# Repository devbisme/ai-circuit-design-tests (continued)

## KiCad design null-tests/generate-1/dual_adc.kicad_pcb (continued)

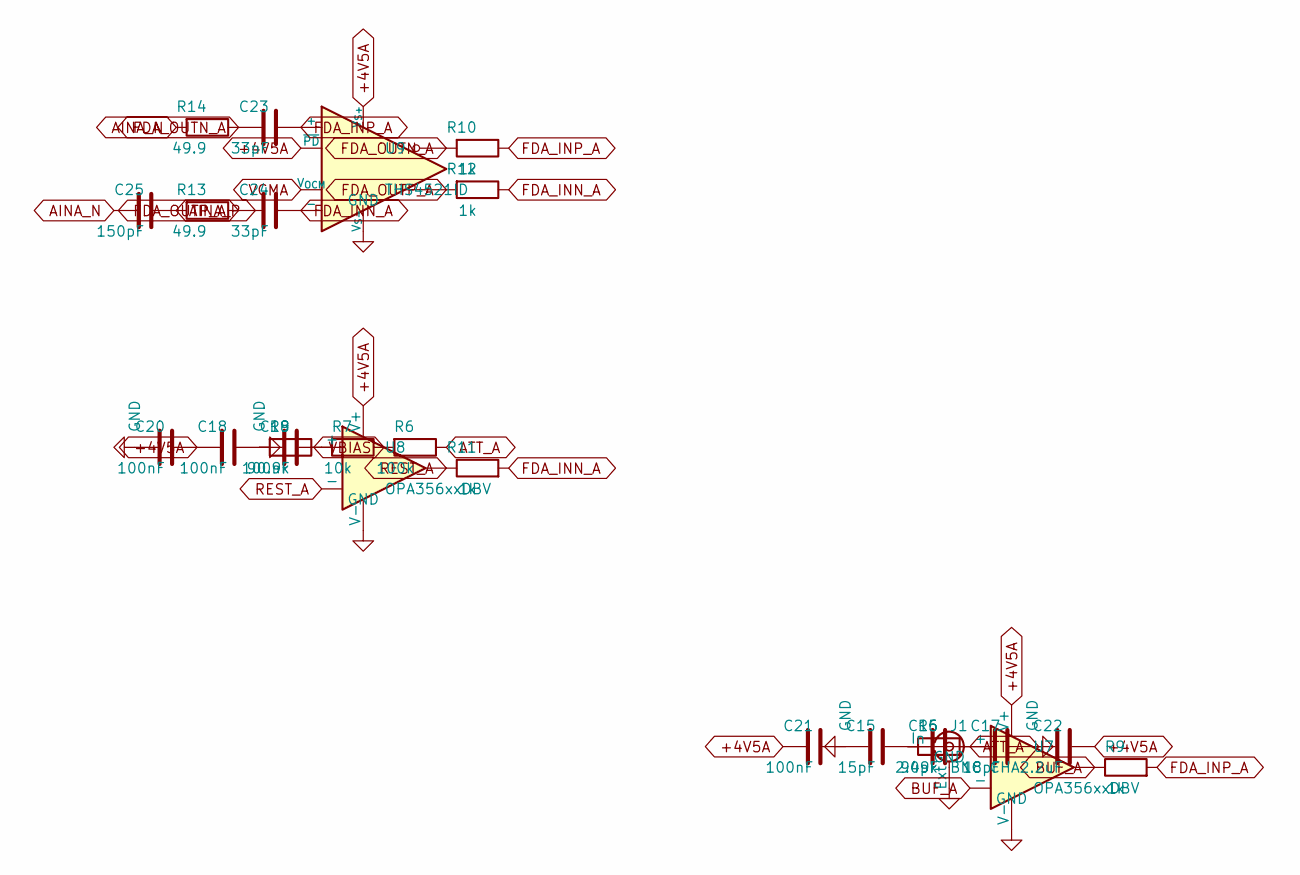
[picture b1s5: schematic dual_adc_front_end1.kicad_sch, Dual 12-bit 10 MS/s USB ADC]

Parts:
C15: 15pF; C_0805_2012Metric
C16: 2.4pF; C_0805_2012Metric
C17: 18pF; C_0603_1608Metric
C18, C20, C21: 100nF; C_0402_1005Metric
C19: 100nF; C_0603_1608Metric
C22: 2.2uF; C_0603_1608Metric
C23, C24: 33pF; C_0603_1608Metric
C25: 150pF; C_0603_1608Metric
J1: BNC CHA; BNC_Amphenol_B6252HB-NPP3G-50_Horizontal
R5: 909k; R_1206_3216Metric
R6: 100k; R_0603_1608Metric
R7: 10k; R_0603_1608Metric
R8: 90.9k; R_0603_1608Metric
R9, R10, R11, R12: 1k; R_0603_1608Metric
R13, R14: 49.9; R_0603_1608Metric
U7, U8: OPA356xxDBV; SOT-23-5
U9: THS4521ID; SOIC-8_3.9x4.9mm_P1.27mm

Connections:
+4V5A: C18.1, C20.1, C21.1, C22.1, U7.5 (V+), U8.5 (V+), U9.3 (V_{S+}), U9.7 (~PD); also elsewhere on the board
AINA_N: C25.2, R14.2; also elsewhere on the board
AINA_P: C25.1, R13.2; also elsewhere on the board
ATT_A: C16.2, C17.1, R5.2, R6.1, U7.3 (+); also elsewhere on the board
BUF_A: R9.1, U7.1, U7.4 (-)
FDA_INN_A: C24.1, R11.2, R12.1, U9.1 (-)
FDA_INP_A: C23.1, R9.2, R10.1, U9.8 (+)
FDA_OUTN_A: C23.2, R10.2, R14.1, U9.5
FDA_OUTP_A: C24.2, R12.2, R13.1, U9.4
GND: C15.2, C17.2, C18.2, C19.2, C20.2, C21.2, C22.2, J1.2 (Ext), R8.2, U7.2 (V-), U8.2 (V-), U9.6 (V_{S-}); also elsewhere on the board
unnamed: C15.1, C16.1, J1.1 (In), R5.1
unnamed: C19.1, R7.2, R8.1, U8.3 (+)
REST_A: R11.1, U8.1, U8.4 (-)
VBIAS: R6.2, R7.1; also elsewhere on the board
VCMA: U9.2 (V_{OCM}); also elsewhere on the board

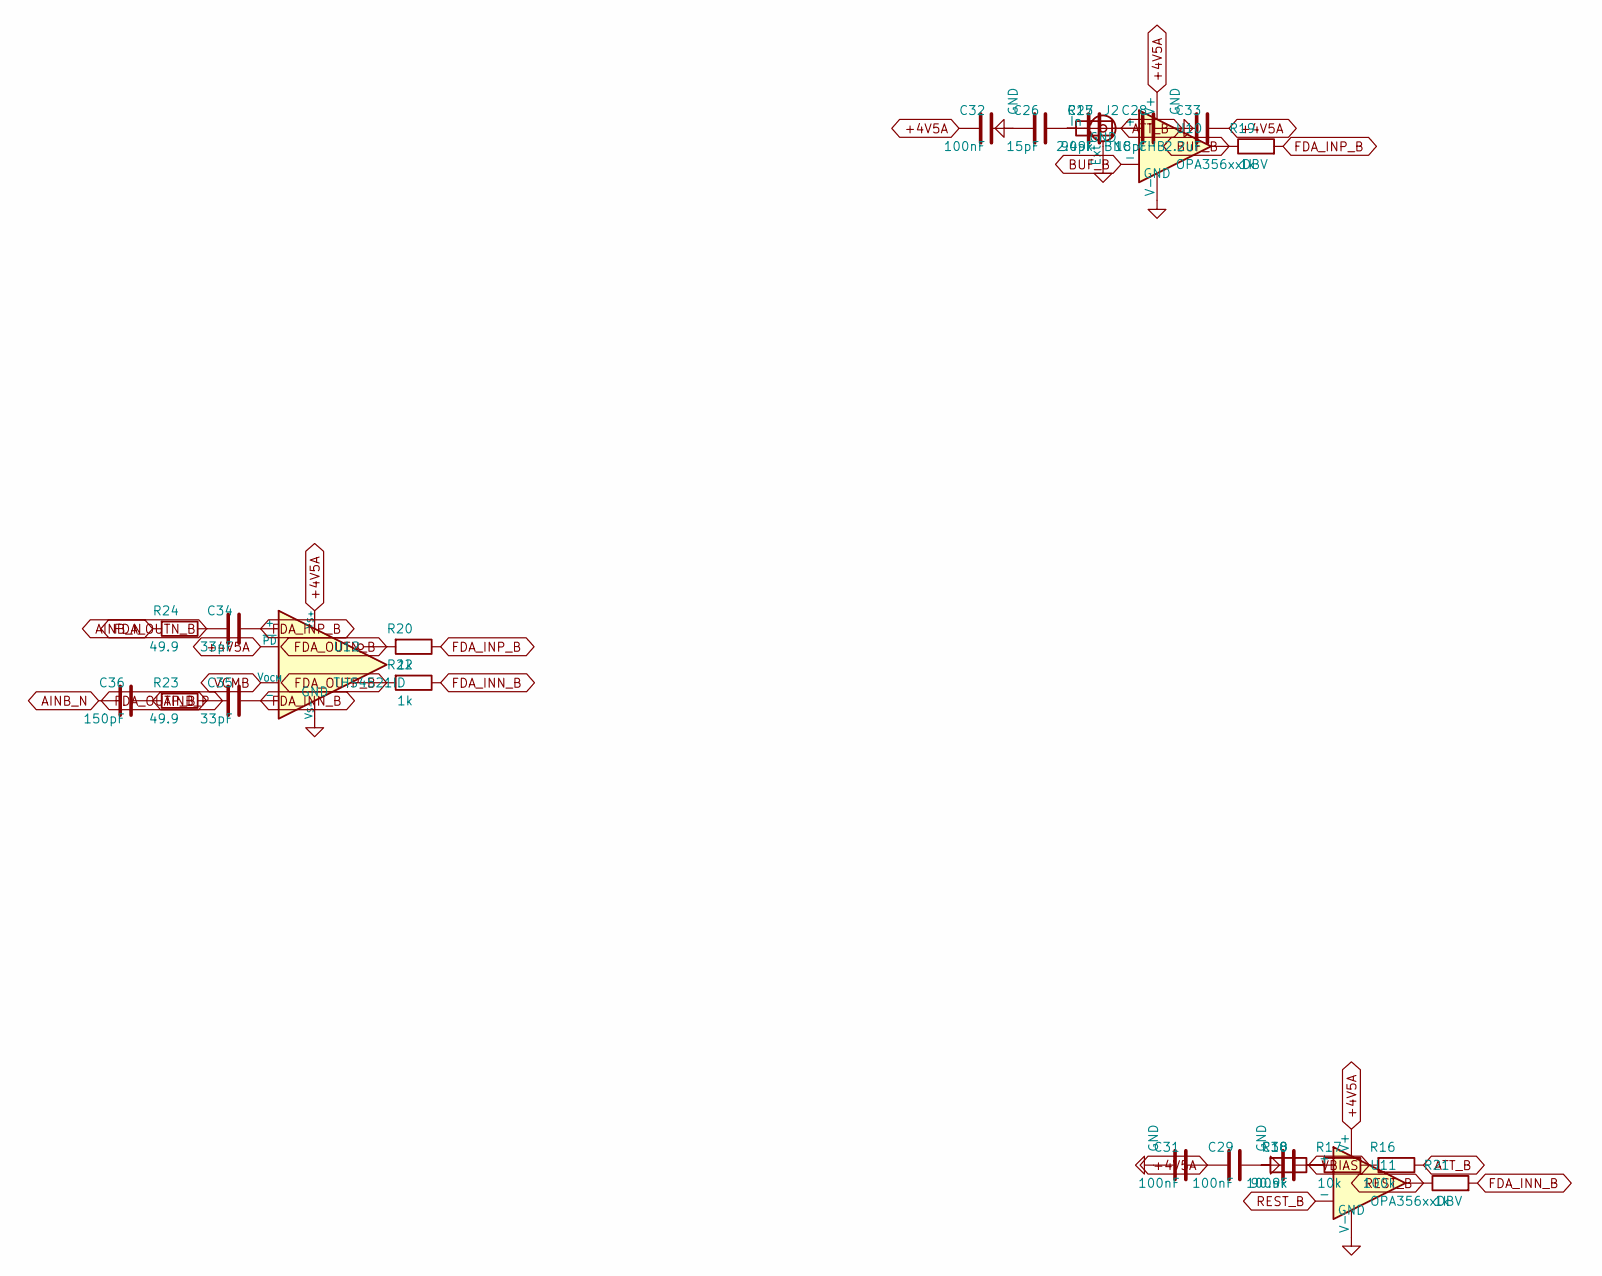
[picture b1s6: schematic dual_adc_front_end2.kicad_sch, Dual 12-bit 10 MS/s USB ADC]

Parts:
C26: 15pF; C_0805_2012Metric
C27: 2.4pF; C_0805_2012Metric
C28: 18pF; C_0603_1608Metric
C29, C31, C32: 100nF; C_0402_1005Metric
C30: 100nF; C_0603_1608Metric
C33: 2.2uF; C_0603_1608Metric
C34, C35: 33pF; C_0603_1608Metric
C36: 150pF; C_0603_1608Metric
J2: BNC CHB; BNC_Amphenol_B6252HB-NPP3G-50_Horizontal
R15: 909k; R_1206_3216Metric
R16: 100k; R_0603_1608Metric
R17: 10k; R_0603_1608Metric
R18: 90.9k; R_0603_1608Metric
R19, R20, R21, R22: 1k; R_0603_1608Metric
R23, R24: 49.9; R_0603_1608Metric
U10, U11: OPA356xxDBV; SOT-23-5
U12: THS4521ID; SOIC-8_3.9x4.9mm_P1.27mm

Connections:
+4V5A: C29.1, C31.1, C32.1, C33.1, U10.5 (V+), U11.5 (V+), U12.3 (V_{S+}), U12.7 (~PD); also elsewhere on the board
AINB_N: C36.2, R24.2; also elsewhere on the board
AINB_P: C36.1, R23.2; also elsewhere on the board
ATT_B: C27.2, C28.1, R15.2, R16.1, U10.3 (+); also elsewhere on the board
BUF_B: R19.1, U10.1, U10.4 (-)
FDA_INN_B: C35.1, R21.2, R22.1, U12.1 (-)
FDA_INP_B: C34.1, R19.2, R20.1, U12.8 (+)
FDA_OUTN_B: C34.2, R20.2, R24.1, U12.5
FDA_OUTP_B: C35.2, R22.2, R23.1, U12.4
GND: C26.2, C28.2, C29.2, C30.2, C31.2, C32.2, C33.2, J2.2 (Ext), R18.2, U10.2 (V-), U11.2 (V-), U12.6 (V_{S-}); also elsewhere on the board
unnamed: C26.1, C27.1, J2.1 (In), R15.1
unnamed: C30.1, R17.2, R18.1, U11.3 (+)
REST_B: R21.1, U11.1, U11.4 (-)
VBIAS: R16.2, R17.1; also elsewhere on the board
VCMB: U12.2 (V_{OCM}); also elsewhere on the board

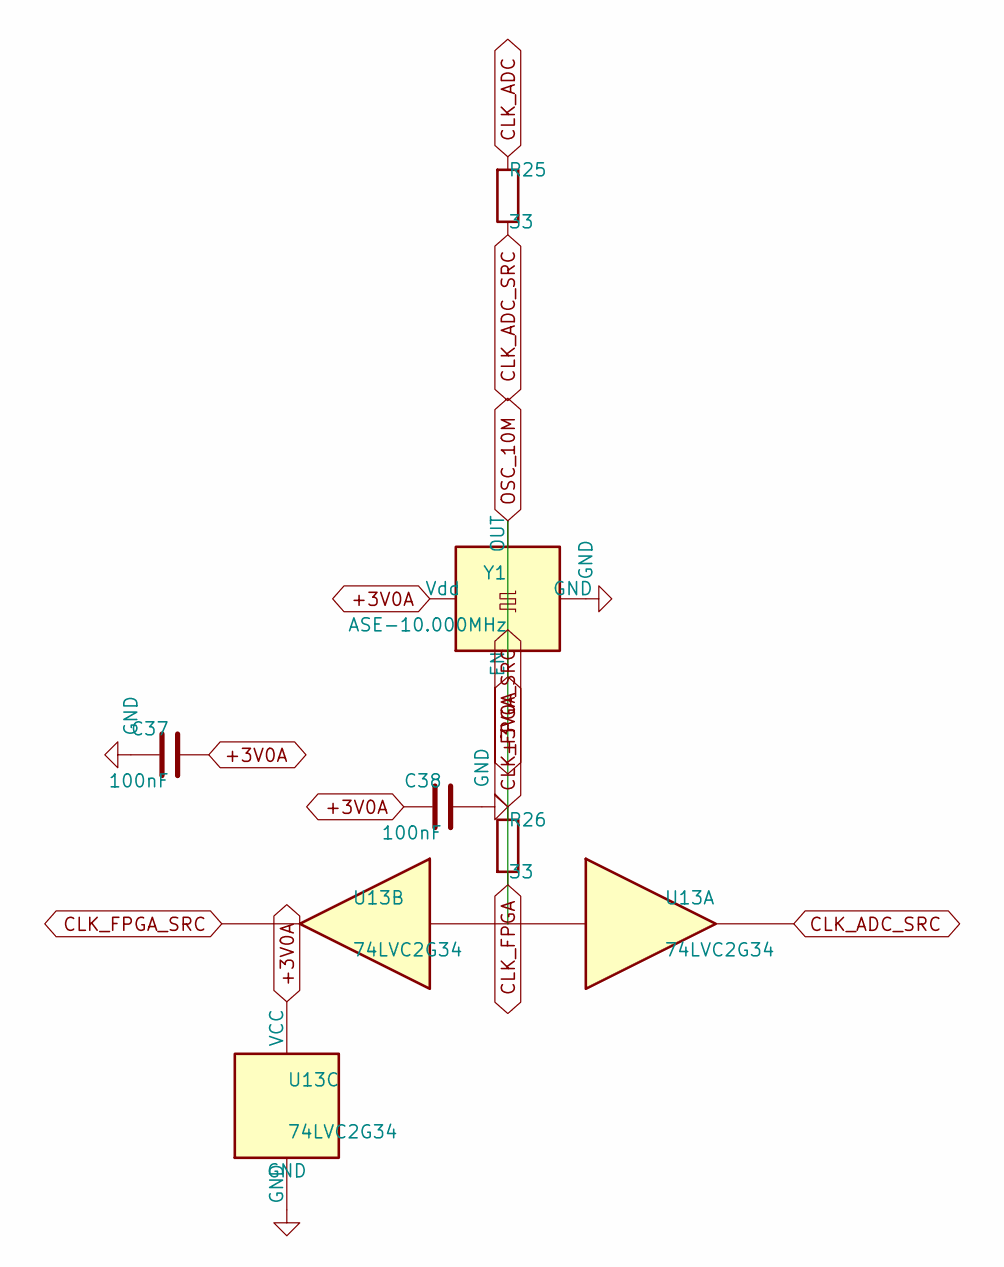
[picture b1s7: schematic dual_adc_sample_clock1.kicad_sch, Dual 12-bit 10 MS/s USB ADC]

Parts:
C37, C38: 100nF; C_0402_1005Metric
R25, R26: 33; R_0603_1608Metric
U13: 74LVC2G34; SOT-363_SC-70-6
Y1: ASE-10.000MHz; Oscillator_SMD_Abracon_ASE-4Pin_3.2x2.5mm

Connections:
CLK_ADC: R25.2; also elsewhere on the board
CLK_ADC_SRC: R25.1, U13.6
GND: C37.2, C38.2, U13.2 (GND), Y1.2 (GND); also elsewhere on the board

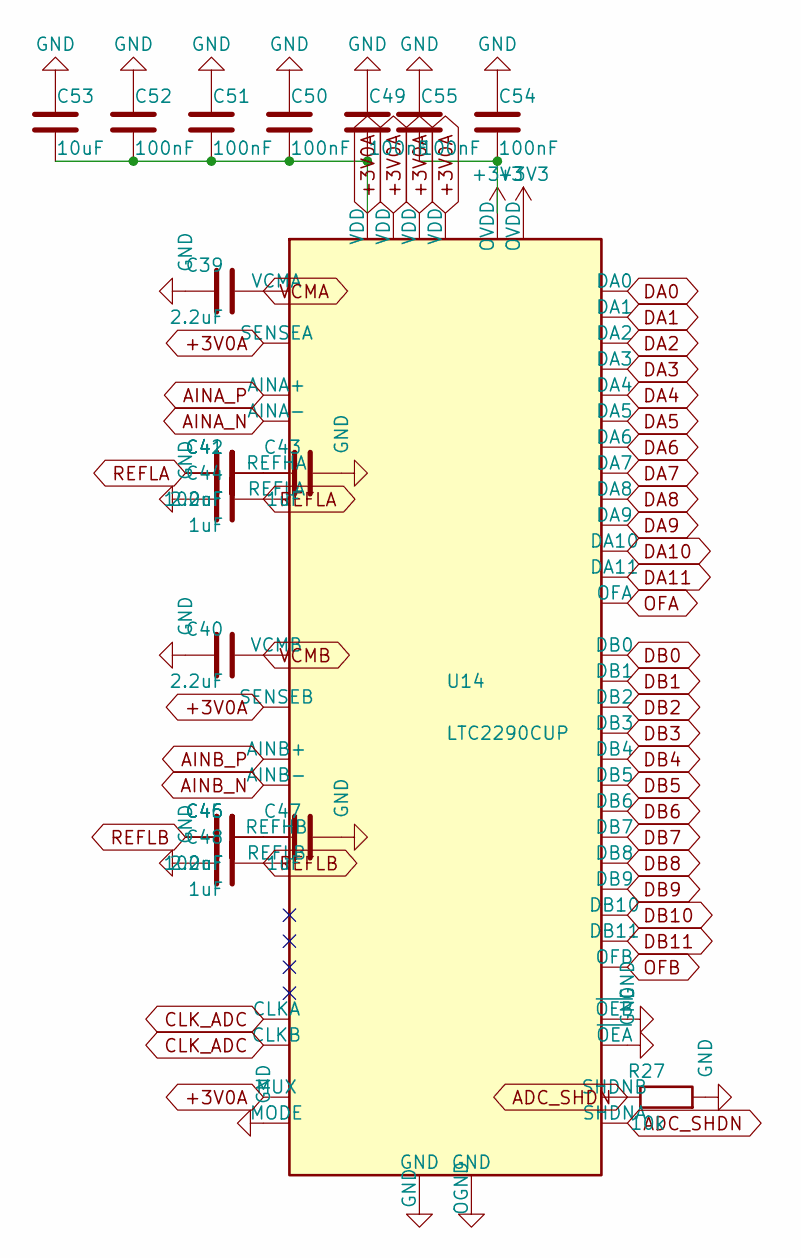
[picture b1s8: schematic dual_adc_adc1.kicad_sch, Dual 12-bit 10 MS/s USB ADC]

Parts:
C39, C40, C42, C46: 2.2uF; C_0603_1608Metric
C41, C45, C49, C50, C51, C52, C54, C55: 100nF; C_0402_1005Metric
C43, C44, C47, C48: 1uF; C_0603_1608Metric
C53: 10uF; C_0805_2012Metric
R27: 10k; R_0603_1608Metric
U14: LTC2290CUP; QFN-64-1EP_9x9mm_P0.5mm_EP7.15x7.15mm

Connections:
+3V3: C54.1, C55.1, U14.32 (OVDD), U14.49 (OVDD); also elsewhere on the board
ADC_SHDN: R27.1, U14.22 (SHDNB), U14.59 (SHDNA); also elsewhere on the board
AINA_N: U14.2 (AINA-); also elsewhere on the board
AINA_P: U14.1 (AINA+); also elsewhere on the board
AINB_N: U14.15 (AINB-); also elsewhere on the board
AINB_P: U14.16 (AINB+); also elsewhere on the board
CLK_ADC: U14.8 (CLKA), U14.9 (CLKB); also elsewhere on the board
DA0: U14.43 (DA0); also elsewhere on the board
DA1: U14.44 (DA1); also elsewhere on the board
DA2: U14.45 (DA2); also elsewhere on the board
DA3: U14.46 (DA3); also elsewhere on the board
DA4: U14.47 (DA4); also elsewhere on the board
DA5: U14.48 (DA5); also elsewhere on the board
DA6: U14.51 (DA6); also elsewhere on the board
DA7: U14.52 (DA7); also elsewhere on the board
DA8: U14.53 (DA8); also elsewhere on the board
DA9: U14.54 (DA9); also elsewhere on the board
DA10: U14.55 (DA10); also elsewhere on the board
DA11: U14.56 (DA11); also elsewhere on the board
DB0: U14.26 (DB0); also elsewhere on the board
DB1: U14.27 (DB1); also elsewhere on the board
DB2: U14.28 (DB2); also elsewhere on the board
DB3: U14.29 (DB3); also elsewhere on the board
DB4: U14.30 (DB4); also elsewhere on the board
DB5: U14.33 (DB5); also elsewhere on the board
DB6: U14.34 (DB6); also elsewhere on the board
DB7: U14.35 (DB7); also elsewhere on the board
DB8: U14.36 (DB8); also elsewhere on the board
DB9: U14.37 (DB9); also elsewhere on the board
DB10: U14.38 (DB10); also elsewhere on the board
DB11: U14.39 (DB11); also elsewhere on the board
GND: C39.2, C40.2, C43.2, C44.2, C47.2, C48.2, C49.2, C50.2, C51.2, C52.2, C53.2, C54.2, C55.2, R27.2, U14.17 (GND), U14.23 (~OEB), U14.31 (OGND), U14.50 (OGND), U14.58 (~OEA), U14.60 (MODE), U14.64 (GND), U14.65 (GND); also elsewhere on the board
unnamed: C41.1, C42.1, C43.1, U14.3 (REFHA), U14.4 (REFHA)
unnamed: C45.1, C46.1, C47.1, U14.13 (REFHB), U14.14 (REFHB)
OFA: U14.57 (OFA); also elsewhere on the board
OFB: U14.40 (OFB); also elsewhere on the board
REFLA: C41.2, C42.2, C44.1, U14.5 (REFLA), U14.6 (REFLA)
REFLB: C45.2, C46.2, C48.1, U14.11 (REFLB), U14.12 (REFLB)
VCMA: C39.1, U14.61 (VCMA); also elsewhere on the board
VCMB: C40.1, U14.20 (VCMB); also elsewhere on the board

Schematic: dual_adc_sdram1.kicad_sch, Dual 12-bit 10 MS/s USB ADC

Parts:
C56, C57, C58, C59, C60, C61, C62: 100nF; C_0402_1005Metric
C63: 10uF; C_0805_2012Metric
U15: IS42S16400J-7TL; TSOP-II-54_22.2x10.16mm_P0.8mm

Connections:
+3V3: C56.1, C57.1, C58.1, C59.1, C60.1, C61.1, C62.1, C63.1, U15.1 (VDD), U15.3 (VDDQ), U15.9 (VDDQ), U15.14 (VDD), U15.27 (VDD), U15.43 (VDDQ), U15.49 (VDDQ); also elsewhere on the board
GND: C56.2, C57.2, C58.2, C59.2, C60.2, C61.2, C62.2, C63.2, U15.6 (GNDQ), U15.12 (GNDQ), U15.28 (GND), U15.41 (GND), U15.46 (GNDQ), U15.52 (GNDQ), U15.54 (GND); also elsewhere on the board
SD_A0: U15.23 (A0); also elsewhere on the board
SD_A1: U15.24 (A1); also elsewhere on the board
SD_A2: U15.25 (A2); also elsewhere on the board
SD_A3: U15.26 (A3); also elsewhere on the board
SD_A4: U15.29 (A4); also elsewhere on the board
SD_A5: U15.30 (A5); also elsewhere on the board
SD_A6: U15.31 (A6); also elsewhere on the board
SD_A7: U15.32 (A7); also elsewhere on the board
SD_A8: U15.33 (A8); also elsewhere on the board
SD_A9: U15.34 (A9); also elsewhere on the board
SD_A10: U15.22 (A10); also elsewhere on the board
SD_A11: U15.35 (A11); also elsewhere on the board
SD_BA0: U15.20 (BA0); also elsewhere on the board
SD_BA1: U15.21 (BA1); also elsewhere on the board
SD_CAS_N: U15.17 (~CAS); also elsewhere on the board
SD_CKE: U15.37 (CKE); also elsewhere on the board
SD_CLK: U15.38 (CLK); also elsewhere on the board
SD_CS_N: U15.19 (~CS); also elsewhere on the board
SD_DQ0: U15.2 (DQ0); also elsewhere on the board
SD_DQ1: U15.4 (DQ1); also elsewhere on the board
SD_DQ2: U15.5 (DQ2); also elsewhere on the board
SD_DQ3: U15.7 (DQ3); also elsewhere on the board
SD_DQ4: U15.8 (DQ4); also elsewhere on the board
SD_DQ5: U15.10 (DQ5); also elsewhere on the board
SD_DQ6: U15.11 (DQ6); also elsewhere on the board
SD_DQ7: U15.13 (DQ7); also elsewhere on the board
SD_DQ8: U15.42 (DQ8); also elsewhere on the board
SD_DQ9: U15.44 (DQ9); also elsewhere on the board
SD_DQ10: U15.45 (DQ10); also elsewhere on the board
SD_DQ11: U15.47 (DQ11); also elsewhere on the board
SD_DQ12: U15.48 (DQ12); also elsewhere on the board
SD_DQ13: U15.50 (DQ13); also elsewhere on the board
SD_DQ14: U15.51 (DQ14); also elsewhere on the board
SD_DQ15: U15.53 (DQ15); also elsewhere on the board
SD_LDQM: U15.15 (LDQM); also elsewhere on the board
SD_RAS_N: U15.18 (~RAS); also elsewhere on the board
SD_UDQM: U15.39 (UDQM); also elsewhere on the board
SD_WE_N: U15.16 (~WE); also elsewhere on the board

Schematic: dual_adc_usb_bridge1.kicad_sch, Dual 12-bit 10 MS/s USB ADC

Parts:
C64, C66, C68, C69, C70, C71, C72, C76: 100nF; C_0402_1005Metric
C65, C67, C73: 4.7uF; C_0805_2012Metric
C74, C75: 18pF; C_0402_1005Metric
R28, R29, R32, R33, R34: 10k; R_0603_1608Metric
R30: 12k; R_0603_1608Metric
R31: 2.2k; R_0603_1608Metric
U16: FT232HL; LQFP-48_7x7mm_P0.5mm
U17: 93LC56B; SOIC-8_3.9x4.9mm_P1.27mm
Y2: 12MHz; Crystal_SMD_3225-4Pin_3.2x2.5mm

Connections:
+3V3: C68.1, C69.1, C70.1, C71.1, C72.1, C73.1, C76.1, R28.2, R29.2, R32.2, R33.2, R34.2, U16.3 (VPHY), U16.8 (VPLL), U16.12 (VCCIO), U16.24 (VCCIO), U16.39 (VCCD), U16.40 (VREGIN), U16.46 (VCCIO), U17.8 (VCC); also elsewhere on the board
FT_CLKOUT: U16.29 (ACBUS5); also elsewhere on the board
FT_D0: U16.13 (ADBUS0); also elsewhere on the board
FT_D1: U16.14 (ADBUS1); also elsewhere on the board
FT_D2: U16.15 (ADBUS2); also elsewhere on the board
FT_D3: U16.16 (ADBUS3); also elsewhere on the board
FT_D4: U16.17 (ADBUS4); also elsewhere on the board
FT_D5: U16.18 (ADBUS5); also elsewhere on the board
FT_D6: U16.19 (ADBUS6); also elsewhere on the board
FT_D7: U16.20 (ADBUS7); also elsewhere on the board
FT_EECLK: R33.1, U16.44 (EECLK), U17.2 (SCLK)
FT_EECS: R32.1, U16.45 (EECS), U17.1 (CS)
FT_EEDATA: R31.2, R34.1, U16.43 (EEDATA), U17.3 (DI)
FT_GPIO8: U16.32 (ACBUS8); also elsewhere on the board
FT_GPIO9: U16.33 (ACBUS9); also elsewhere on the board
FT_OE_N: U16.30 (ACBUS6); also elsewhere on the board
FT_RD_N: U16.26 (ACBUS2); also elsewhere on the board
FT_RXF_N: U16.21 (ACBUS0); also elsewhere on the board
FT_SIWU_N: U16.28 (ACBUS4); also elsewhere on the board
FT_TXE_N: U16.25 (ACBUS1); also elsewhere on the board
FT_WR_N: U16.27 (ACBUS3); also elsewhere on the board
FT_XI: C74.1, U16.1 (XCSI), Y2.1
FT_XO: C75.1, U16.2 (XCSO), Y2.3
GND: C64.2, C65.2, C66.2, C67.2, C68.2, C69.2, C70.2, C71.2, C72.2, C73.2, C74.2, C75.2, C76.2, R30.2, U16.4 (AGND), U16.9 (AGND), U16.10 (GND), U16.11 (GND), U16.22 (GND), U16.23 (GND), U16.35 (GND), U16.36 (GND), U16.41 (AGND), U16.42 (TEST), U16.47 (GND), U16.48 (GND), U17.5 (GND), Y2.2 (G), Y2.4 (G); also elsewhere on the board
unnamed: R28.1, U16.31 (ACBUS7)
unnamed: R30.1, U16.5 (REF)
unnamed: C64.1, C65.1, U16.37 (VCCA)
unnamed: C66.1, C67.1, U16.38 (VCCCORE)
unnamed: R29.1, U16.34 (~RESET)
unnamed: R31.1, U17.4 (DO)
USB_DN: U16.6 (DM); also elsewhere on the board
USB_DP: U16.7 (DP); also elsewhere on the board

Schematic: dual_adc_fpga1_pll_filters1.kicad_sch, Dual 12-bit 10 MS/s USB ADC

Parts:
C78, C80: 100nF; C_0402_1005Metric
C79, C81: 10uF; C_0805_2012Metric
R44, R45: 100; R_0603_1608Metric

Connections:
+1V2: R44.1, R45.1; also elsewhere on the board
GND: C78.2, C79.2, C80.2, C81.2; also elsewhere on the board
VCCPLL0: C78.1, C79.1, R44.2; also elsewhere on the board
VCCPLL1: C80.1, C81.1, R45.2; also elsewhere on the board

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
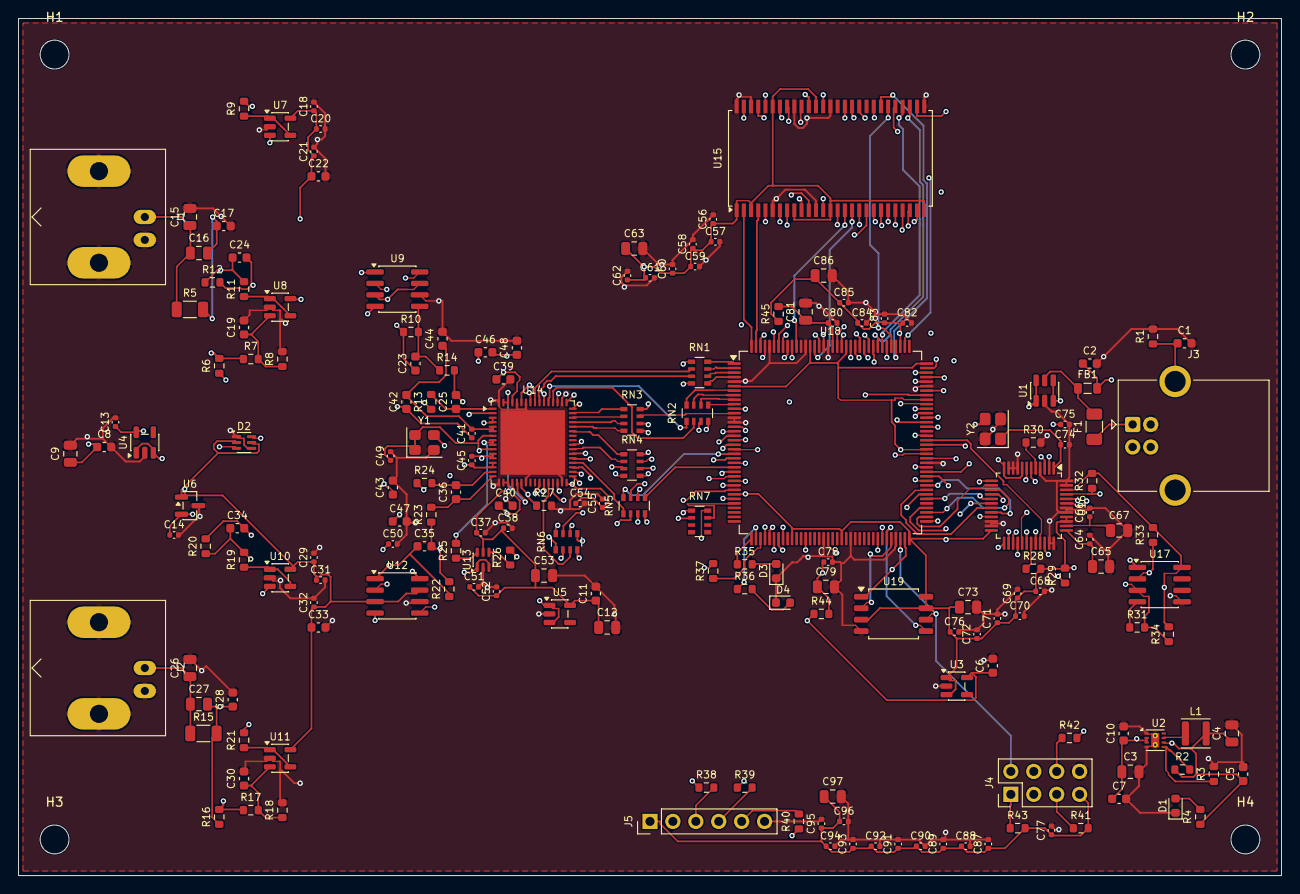
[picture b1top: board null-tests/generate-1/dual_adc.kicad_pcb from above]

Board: 4 copper layers, 140.0 x 95.0 mm, 186 parts (0 on the bottom side), 187 nets.

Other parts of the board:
H1, H2, H3, H4: MountingHole; MountingHole_3.2mm_M3

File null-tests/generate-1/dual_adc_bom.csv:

"Refs","Value","Spec","Footprint","Qty"
"C1","4.7nF","","Capacitor_SMD:C_0603_1608Metric","1"
"C2,C22,C33,C39,C40,C42,C46","2.2uF","","Capacitor_SMD:C_0603_1608Metric","7"
"C3,C65,C67,C73","4.7uF","","Capacitor_SMD:C_0805_2012Metric","4"
"C4","22uF","","Capacitor_SMD:C_0805_2012Metric","1"
"C5-C8,C10,C11,C43,C44,C47,C48","1uF","","Capacitor_SMD:C_0603_1608Metric","10"
"C9,C12,C53,C63,C79,C81,C86,C97","10uF","","Capacitor_SMD:C_0805_2012Metric","8"
"C13,C14,C18,C20,C21,C29,C31,C32,C37,C38,C41,C45,C49-C52,C54-C62,C64,C66,C68-C72,C76-C78,C80,C82-C85,C87-C96","100nF","","Capacitor_SMD:C_0402_1005Metric","50"
"C15,C26","15pF","C0G 100V","Capacitor_SMD:C_0805_2012Metric","2"
"C16,C27","2.4pF","C0G 100V","Capacitor_SMD:C_0805_2012Metric","2"
"C17,C28","18pF","C0G","Capacitor_SMD:C_0603_1608Metric","2"
"C19,C30","100nF","","Capacitor_SMD:C_0603_1608Metric","2"
"C23,C24,C34,C35","33pF","C0G","Capacitor_SMD:C_0603_1608Metric","4"
"C25,C36","150pF","C0G","Capacitor_SMD:C_0603_1608Metric","2"
"C74,C75","18pF","","Capacitor_SMD:C_0402_1005Metric","2"
"D1","GRN","","LED_SMD:LED_0603_1608Metric","1"
"D2","BAV199DW","","Package_TO_SOT_SMD:SOT-363_SC-70-6","1"
"D3,D4","YEL","","LED_SMD:LED_0603_1608Metric","2"
"F1","500mA","","Fuse:Fuse_1206_3216Metric","1"
"FB1","600R@100MHz","","Inductor_SMD:L_0805_2012Metric","1"
"J1","BNC CHA","","Connector_Coaxial:BNC_Amphenol_B6252HB-NPP3G-50_Horizontal","1"
"J2","BNC CHB","","Connector_Coaxial:BNC_Amphenol_B6252HB-NPP3G-50_Horizontal","1"
"J3","USB_B","","Connector_USB:USB_B_OST_USB-B1HSxx_Horizontal","1"
"J4","FPGA_PROG","","Connector_PinHeader_2.54mm:PinHeader_2x04_P2.54mm_Vertical","1"
"J5","GPIO/TRIG","","Connector_PinHeader_2.54mm:PinHeader_1x06_P2.54mm_Vertical","1"
"L1","2.2uH","","Inductor_SMD:L_Changjiang_FNR3015S","1"
"R1","1M","","Resistor_SMD:R_0603_1608Metric","1"
"R2","316k","","Resistor_SMD:R_0603_1608Metric","1"
"R3","100k","","Resistor_SMD:R_0603_1608Metric","1"
"R4","1k","","Resistor_SMD:R_0603_1608Metric","1"
"R5,R15","909k","0.1%, 200V","Resistor_SMD:R_1206_3216Metric","2"
"R6,R16","100k","0.1%","Resistor_SMD:R_0603_1608Metric","2"
"R7,R17","10k","0.1%","Resistor_SMD:R_0603_1608Metric","2"
"R8,R18","90.9k","0.1%","Resistor_SMD:R_0603_1608Metric","2"
"R9-R12,R19-R22","1k","0.1%","Resistor_SMD:R_0603_1608Metric","8"
"R13,R14,R23,R24","49.9","","Resistor_SMD:R_0603_1608Metric","4"
"R25,R26","33","","Resistor_SMD:R_0603_1608Metric","2"
"R27-R29,R32-R34,R41-R43","10k","","Resistor_SMD:R_0603_1608Metric","9"
"R30","12k","1%","Resistor_SMD:R_0603_1608Metric","1"
"R31","2.2k","","Resistor_SMD:R_0603_1608Metric","1"
"R35,R36","330","","Resistor_SMD:R_0603_1608Metric","2"
"R37-R40,R44,R45","100","","Resistor_SMD:R_0603_1608Metric","6"
"RN1-RN7","33","","Resistor_SMD:R_Array_Convex_4x0603","7"
"U1","USBLC6-2SC6","","Package_TO_SOT_SMD:SOT-23-6","1"
"U2","TPS62160DSG","","Package_SON:WSON-8-1EP_2x2mm_P0.5mm_EP0.9x1.6mm_ThermalVias","1"
"U3","AP2112K-1.2","","Package_TO_SOT_SMD:SOT-23-5","1"
"U4","LP5907MFX-4.5","","Package_TO_SOT_SMD:SOT-23-5","1"
"U5","LP5907MFX-3.0","","Package_TO_SOT_SMD:SOT-23-5","1"
"U6","REF3020","","Package_TO_SOT_SMD:SOT-23","1"
"U7,U8,U10,U11","OPA356xxDBV","","Package_TO_SOT_SMD:SOT-23-5","4"
"U9,U12","THS4521ID","","Package_SO:SOIC-8_3.9x4.9mm_P1.27mm","2"
"U13","74LVC2G34","","Package_TO_SOT_SMD:SOT-363_SC-70-6","1"
"U14","LTC2290CUP","","Package_DFN_QFN:QFN-64-1EP_9x9mm_P0.5mm_EP7.15x7.15mm","1"
"U15","IS42S16400J-7TL","","Package_SO:TSOP-II-54_22.2x10.16mm_P0.8mm","1"
"U16","FT232HL","","Package_QFP:LQFP-48_7x7mm_P0.5mm","1"
"U17","93LC56B","","Package_SO:SOIC-8_3.9x4.9mm_P1.27mm","1"
"U18","ICE40HX4K-TQ144","","Package_QFP:TQFP-144_20x20mm_P0.5mm","1"
"U19","W25Q32JVSS","","Package_SO:SOIC-8_5.3x5.3mm_P1.27mm","1"
"Y1","ASE-10.000MHz","","Oscillator:Oscillator_SMD_Abracon_ASE-4Pin_3.2x2.5mm","1"
"Y2","12MHz","","Crystal:Crystal_SMD_3225-4Pin_3.2x2.5mm","1"
